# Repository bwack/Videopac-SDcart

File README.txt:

This project is under construction.
The design files are not currently stable.

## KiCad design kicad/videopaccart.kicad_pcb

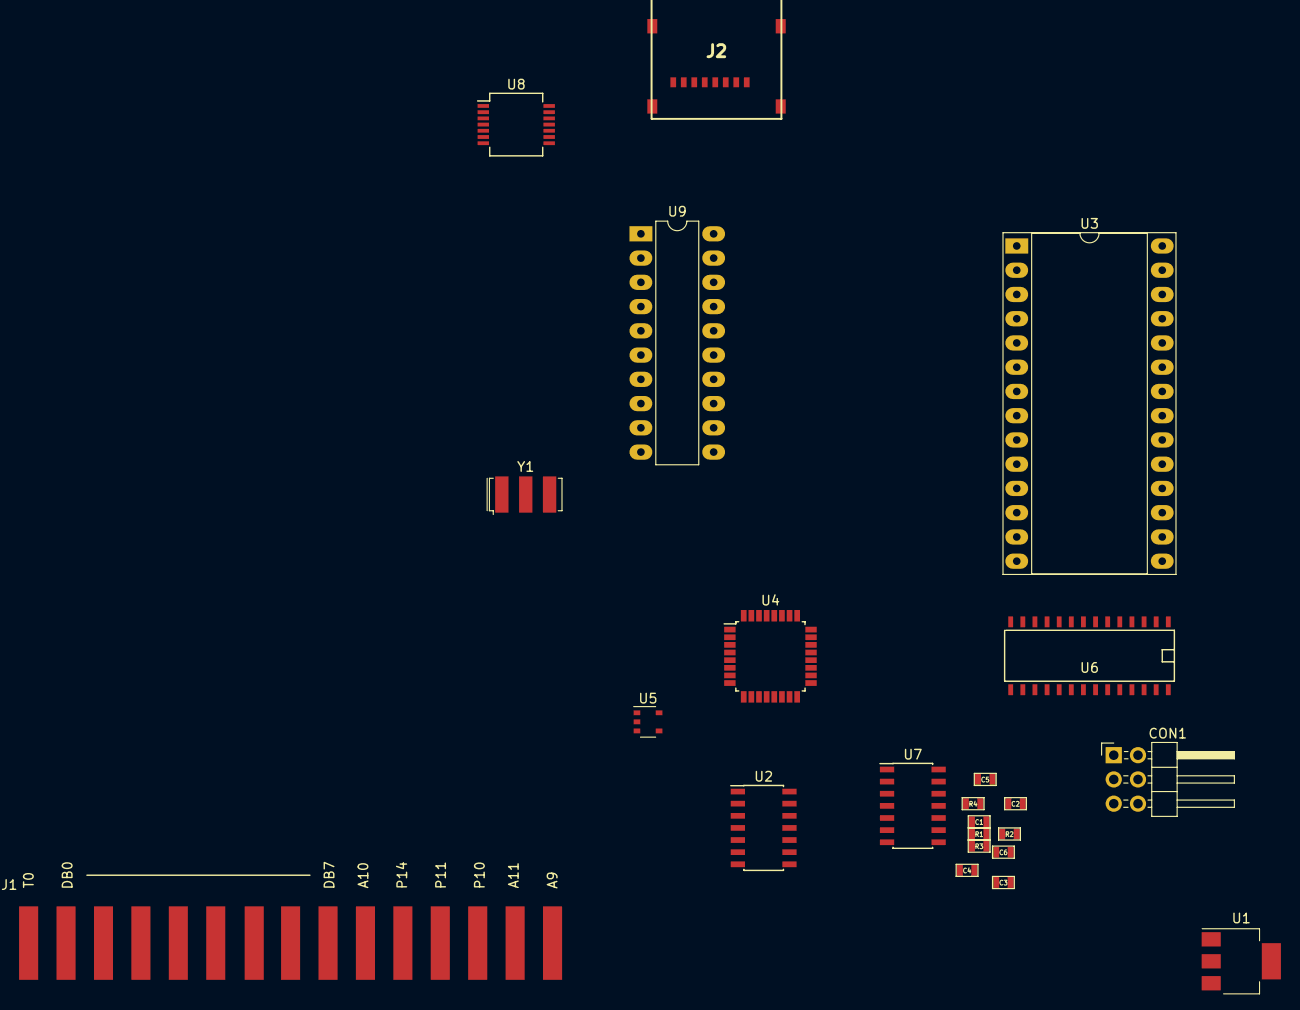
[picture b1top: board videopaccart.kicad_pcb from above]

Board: 2 copper layers, 23 parts (0 on the bottom side), 60 nets, no tracks yet.

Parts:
C1, C2, C3, C4, C5, C6: C; SM0603
CON1: AVR-ISP-6; Pin_Header_Angled_2x03_Pitch2.54mm
J1: Videopac_Cart_Edge_Conn; videopac-edgecon
J2: MICRO_SD_HINGE; MICRO_SD_HINGE_AMP
R1, R2, R3, R4: R; SM0603
U1: AP111733; SOT-223
U2, U7: 74LS02; SOIC-14_3.9x8.7mm_Pitch1.27mm
U3: 27128; DIP-28_W15.24mm_Socket_LongPads
U4: ATMEGA328P-AU; LQFP-32_7x7mm_Pitch0.8mm
U5: 74LVC1G00; TSOP-5_1.65x3.05mm_Pitch0.95mm
U6: HM62256BLP-7; SOIC-28
U8: 74LS125; SSOP-14_5.3x6.2mm_Pitch0.65mm
U9: 74LS245; DIP-20_W7.62mm_LongPads
Y1: Resonator; Resonator_SMD-3pin_7.2x3.0mm

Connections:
#SS: U4.14, U8.1, U8.4, U8.10, U8.13
+3V3: C2.1, J2.4, U1.2, U1.4, U8.14
/#PSEN: J1.F, U2.3, U3.20
/#RAM_CS: U2.10, U6.22
/#RD: U2.4, U7.6
/#ROM_OE: U3.22, U7.1
/A0: J1.G, U3.10, U6.10
/A1: J1.H, U3.9, U6.9
/A2: J1.J, U3.8, U6.8
/A3: J1.K, U3.7, U6.7
/A4: J1.L, U3.6, U6.6
/A5: J1.M, U3.5, U6.5
/A6: J1.P, U3.4, U6.4
/A7: J1.N, U3.3, U6.3
/A8: J1.R, U3.25, U6.25
/A9: J1.15, U3.24, U6.24
/A10: J1.10, U3.21, U6.21
/A11: J1.14, U3.23, U6.23
/A12: J1.13, U3.2, U6.2
/A13: U3.26, U6.26
/A13_TXD: J1.12, U4.25
/CS33: J2.2, U8.8
/D0: J1.2, U3.11, U6.11, U9.18
/D1: J1.3, U3.12, U6.12, U9.17
/D2: J1.4, U3.13, U6.13, U9.16
/D3: J1.5, U3.15, U6.15, U9.15
/D4: J1.6, U3.16, U6.16, U9.14
/D5: J1.7, U3.17, U6.17, U9.13
/D6: J1.8, U3.18, U6.18, U9.12
/D7: J1.9, U3.19, U6.19, U9.11
/MISO33: J2.7, U8.12
/MOSI33: J2.3, U8.3
/RD: J1.E, U2.5, U2.6, U5.1, U7.2
/SCK33: J2.5, U8.6
GND: C1.2, C2.2, C3.2, C4.2, C5.2, C6.2, CON1.6, J1.B, J1.C, J2.6, J2.9, J2.10, J2.11, J2.12, U1.1, U2.7, U3.14, U4.3, U4.5, U4.21, U5.3, U6.14, U7.7, U7.8, U7.9, U7.11, U7.12, U8.7, U9.10, Y1.2
MENU: U2.2, U2.11, U2.12, U4.12
MISO: R4.1, U8.11
MOSI: R3.1, U8.2
unnamed: CON1.1, R4.2, U4.16
unnamed: CON1.3, R2.2, U4.17
unnamed: CON1.4, R3.2, U4.15
unnamed: CON1.5, U4.29
unnamed: J1.11, U5.2
unnamed: U2.1, U2.8
unnamed: U2.9, U7.4
unnamed: U2.13, U7.3, U7.5
unnamed: U4.1, U9.5
unnamed: U4.2, U9.6
unnamed: U4.7, Y1.3
unnamed: U4.8, Y1.1
unnamed: U4.9, U9.7
unnamed: U4.10, U9.8
unnamed: U4.11, U9.9
unnamed: U4.23, U9.2
unnamed: U4.24, U9.3
unnamed: U4.32, U9.4
unnamed: U5.4, U6.27, U9.19
SCK: R2.1, U8.5
T0: J1.1, R1.1, U4.13
VCC: C1.1, C3.1, C4.1, C5.1, C6.1, CON1.2, J1.D, R1.2, U1.3, U2.14, U3.28, U4.4, U4.6, U6.28, U7.14, U9.1, U9.20

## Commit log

2018-04-21 :tada: Added .gitattributes & .gitignore files
2018-04-21 the readme
2018-04-21 moving files around
2018-04-21 split send function to transfer.h
2018-04-21 arduino receives commands by serial bitbang + kicad files
2018-04-22 trying to display more than one line of text
2018-04-28 Commits before video8
2018-05-09 test
2018-05-09 revert test
2018-05-12 Edge connector signal names silks
2018-05-12 src cleanup
